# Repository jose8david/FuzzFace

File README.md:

# FuzzFace
Construye tu primer pedal de guitarra

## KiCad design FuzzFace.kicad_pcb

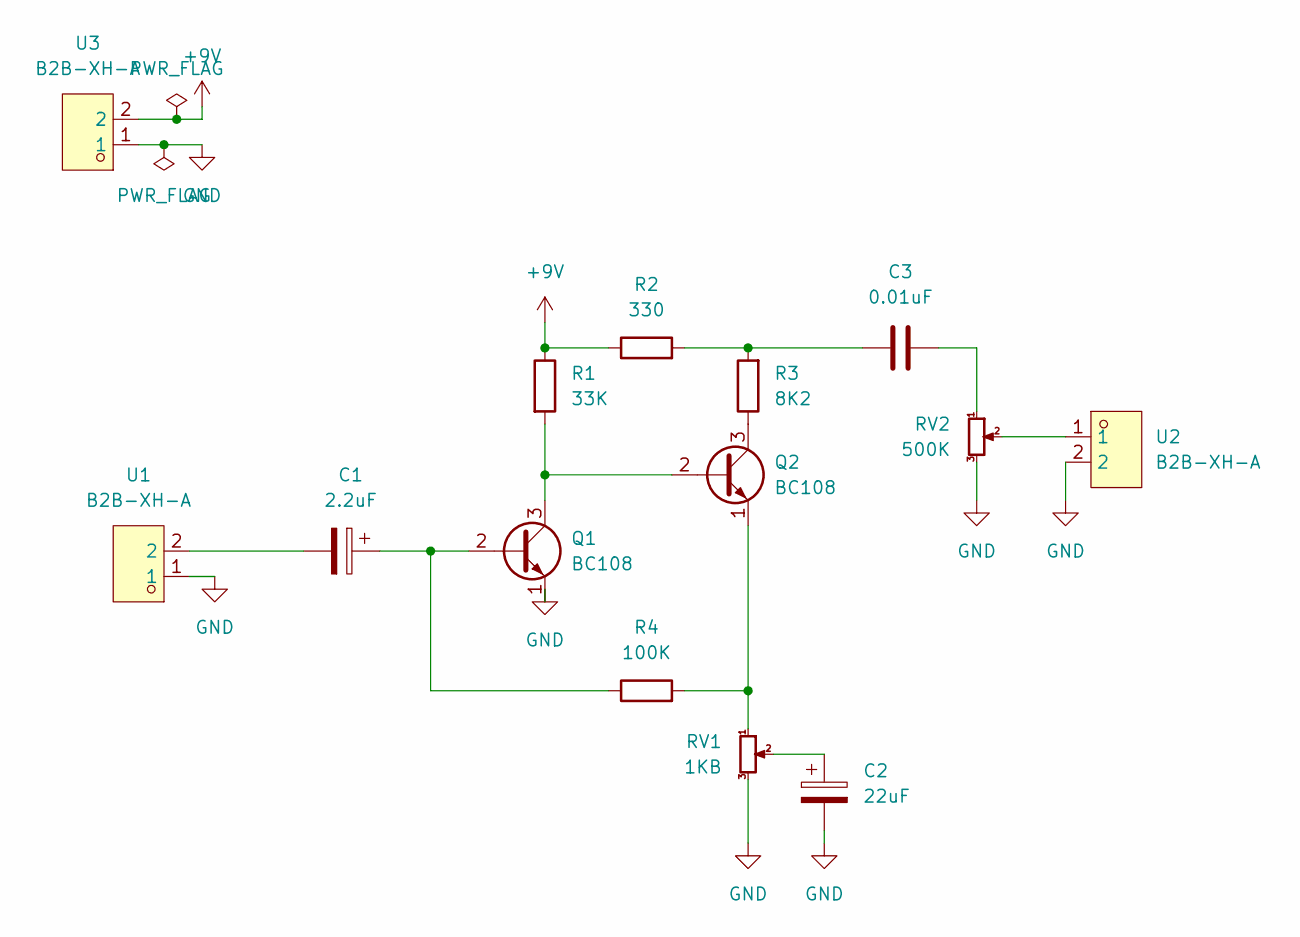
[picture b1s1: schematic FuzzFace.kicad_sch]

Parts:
C1: 2.2uF; C_Radial_D6.3mm_H11.0mm_P2.50mm
C2: 22uF; C_Radial_D6.3mm_H11.0mm_P2.50mm
C3: 0.01uF; C_Radial_D6.3mm_H11.0mm_P2.50mm
Q1, Q2: BC108; TO-18-3
R1: 33K; R_Axial_DIN0411_L9.9mm_D3.6mm_P15.24mm_Horizontal
R2: 330; R_Axial_DIN0411_L9.9mm_D3.6mm_P15.24mm_Horizontal
R3: 8K2; R_Axial_DIN0411_L9.9mm_D3.6mm_P15.24mm_Horizontal
R4: 100K; R_Axial_DIN0411_L9.9mm_D3.6mm_P15.24mm_Horizontal
RV1: 1KB; JST_EH_B3B-EH-A_1x03_P2.50mm_Vertical
RV2: 500K; JST_EH_B3B-EH-A_1x03_P2.50mm_Vertical
U1, U2, U3: B2B-XH-A; CONN-TH_XH-2A; LCSC Part C19272845

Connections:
+9V: R1.1, R2.1, U3.2
GND: C2.2, Q1.1 (E), RV1.3, RV2.3, U1.1, U2.2, U3.1
unnamed: C1.2, U1.2
unnamed: C2.1, RV1.2
unnamed: C3.1, R2.2, R3.2
unnamed: C3.2, RV2.1
unnamed: C1.1, Q1.2 (B), R4.1
unnamed: Q1.3 (C), Q2.2 (B), R1.2
unnamed: Q2.3 (C), R3.1
unnamed: Q2.1 (E), R4.2, RV1.1
unnamed: RV2.2, U2.1

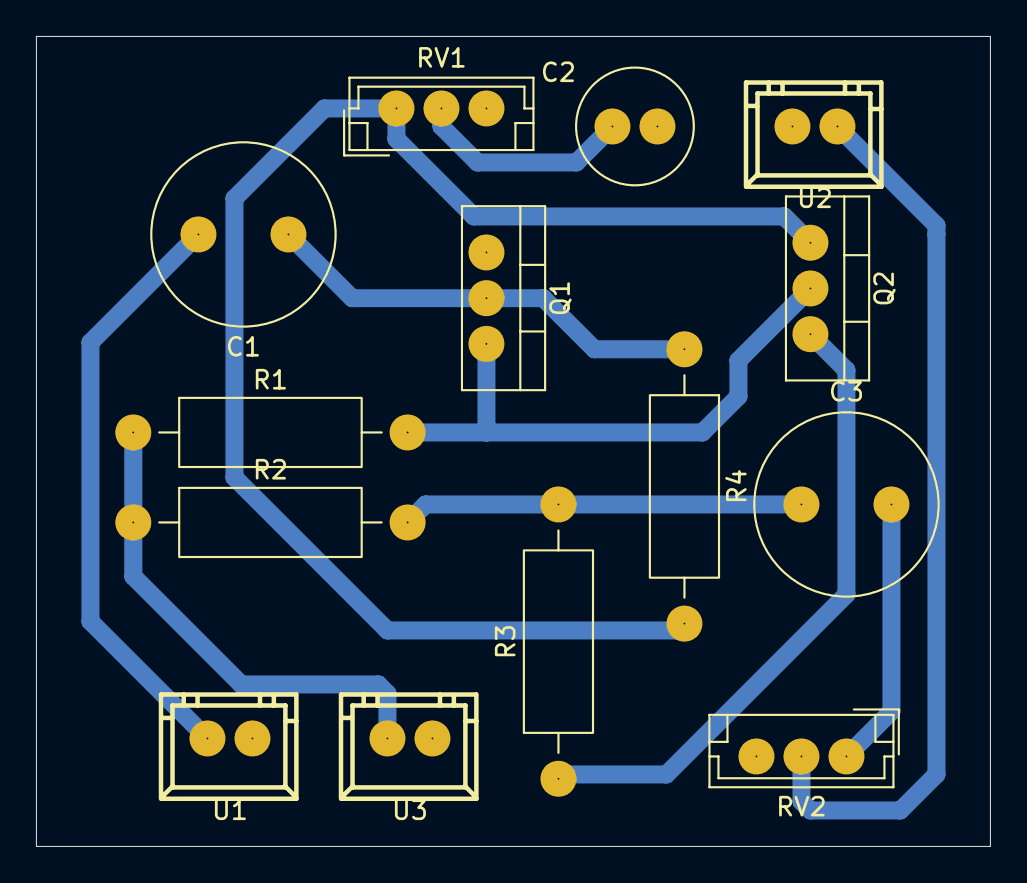
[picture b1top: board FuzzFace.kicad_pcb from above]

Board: 2 copper layers, 53.0 x 45.0 mm, 14 parts (0 on the bottom side), 11 nets.
